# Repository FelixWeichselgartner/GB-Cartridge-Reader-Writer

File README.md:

# GB-Cartridge-Reader-Writer

This is an Arduino Shield, that can be used to dump GameBoy cartridges. This project is strongly inspired by this project:

* https://www.insidegadgets.com/2011/03/19/gbcartread-arduino-based-gameboy-cart-reader-%E2%80%93-part-1-read-the-rom/
* https://github.com/insidegadgets/GBCartRead

The code in this repo is based on this, however I did a lot of changes to the Arduino code.

# Tested ROMs

| Game                   | Dump ROM | Dump RAM | Upload RAM |
|------------------------|----------|----------|------------|
| Tetris (no MBC)        | yes      | N/A      | N/A        |
| Yoshi's Cookie (MBC1)  | yes      | N/A      | N/A        |
| Pokémon Red (MBC5)     | yes      | ?        | ?          |
| Pokémon Yellow (MBC5)  | yes      | yes      | ?          |
| Pokémon TCG (MBC5)     | yes      | yes      | ?          |

GBC is not supported so far.

# Eagle Layout for the Arduino shield

The bottom layer is supposed to be wired with a simple wire to be able to use a single layer pcb.

Used libraries (see submodules):

* https://github.com/adafruit/Adafruit-Eagle-Library
* https://github.com/robelix/rlx-eagle-libs
* https://github.com/JRodrigoTech/Eagle-Libraries

# License

Copyright (c) 2011-2016 by insideGadgets

Copyright (c) 2019-2020 by Felix Weichselgartner (on the changes)

Creative Commons - Attribution-NonCommercial 3.0 Unported (see License.txt)

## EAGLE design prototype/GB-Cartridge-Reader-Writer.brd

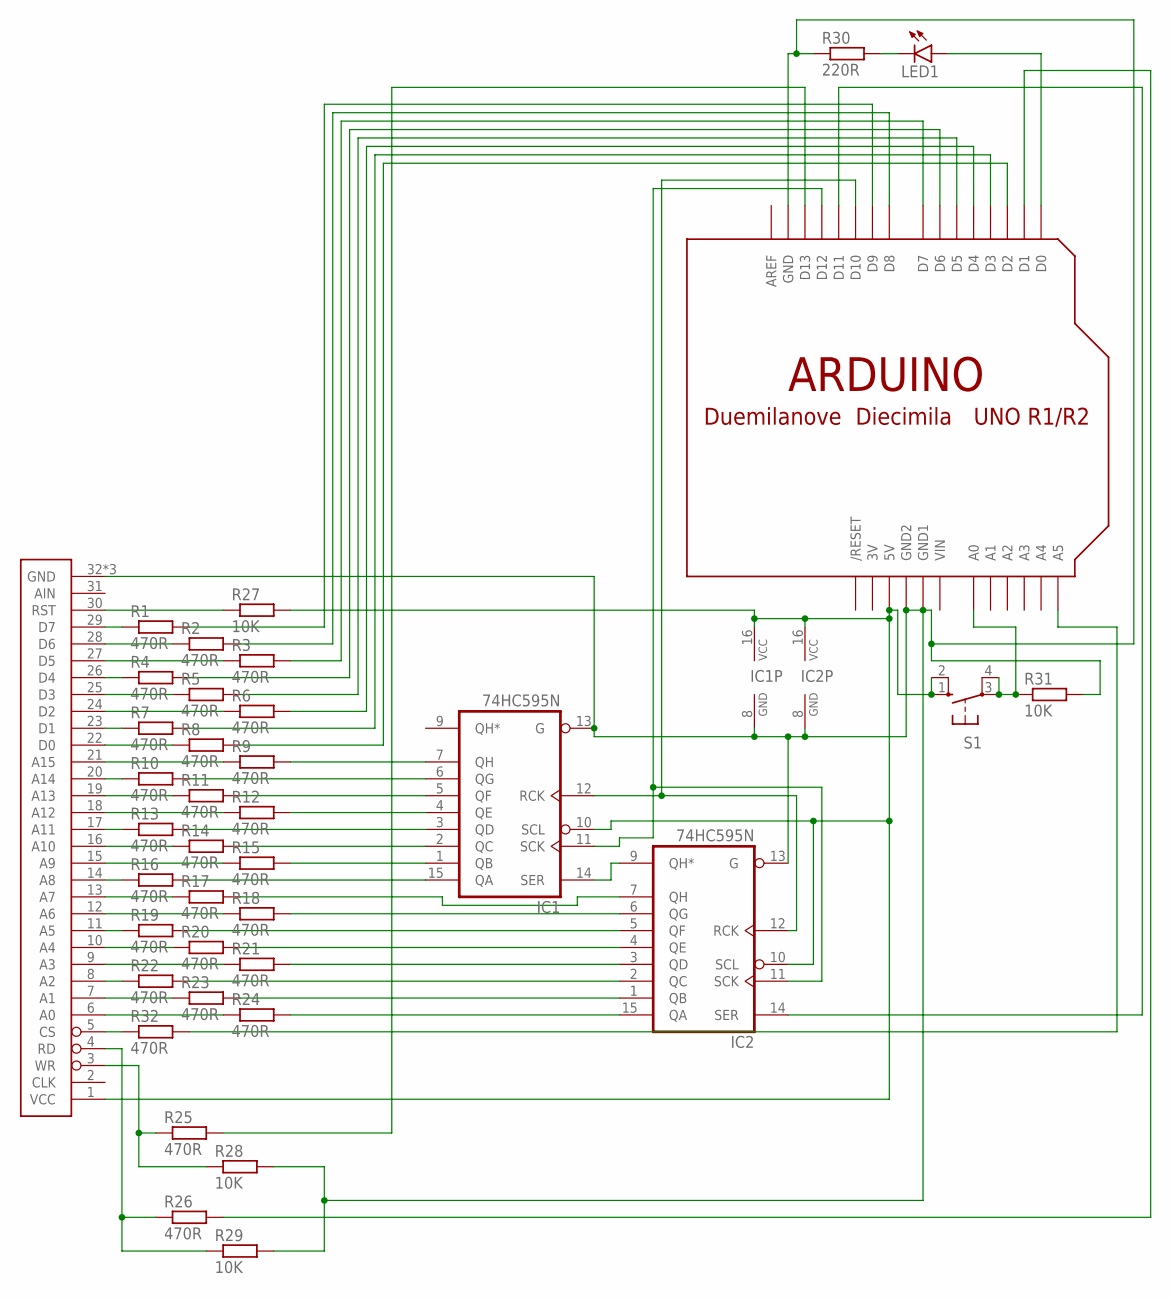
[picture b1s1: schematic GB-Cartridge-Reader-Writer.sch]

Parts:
IC1, IC2: 74HC595N; DIL16
LED1: LED5MM
R1, R2, R3, R4, R5, R6, R7, R8, R9, R10, R11, R12, R13, R14, R15, R16, R17, R18, R19, R20, R21, R22, R23, R24, R25, R26, R32: 470R; 0207/10
R27, R28, R29, R31: 10K; 0207/10
R30: 220R; 0207/10
S1: 10-XX; B3F-10XX
U$1: ARDUINO-NOHOLE
U$2: GB-CARTRIDGE-SLOTV3; GB-CARTRIDGE-SLOT-3

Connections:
3V: U$1.3V
unnamed: R1.1, U$2.29 (D7)
unnamed: R2.1, U$2.28 (D6)
unnamed: R3.1, U$2.27 (D5)
unnamed: R4.1, U$2.26 (D4)
unnamed: R5.1, U$2.25 (D3)
unnamed: R6.1, U$2.24 (D2)
unnamed: R7.1, U$2.23 (D1)
unnamed: R8.1, U$2.22 (D0)
unnamed: R9.1, U$2.21 (A15)
unnamed: R10.1, U$2.20 (A14)
unnamed: R11.1, U$2.19 (A13)
unnamed: R12.1, U$2.18 (A12)
unnamed: R13.1, U$2.17 (A11)
unnamed: R14.1, U$2.16 (A10)
unnamed: R15.1, U$2.15 (A9)
unnamed: R16.1, U$2.14 (A8)
unnamed: R17.1, U$2.13 (A7)
unnamed: R18.1, U$2.12 (A6)
unnamed: R19.1, U$2.11 (A5)
unnamed: R20.1, U$2.10 (A4)
unnamed: R21.1, U$2.9 (A3)
unnamed: R22.1, U$2.8 (A2)
unnamed: R23.1, U$2.7 (A1)
unnamed: R24.1, U$2.6 (A0)
unnamed: IC2.15 (QA), R24.2
unnamed: IC2.1 (QB), R23.2
unnamed: R32.1, U$2.5 (CS)
unnamed: IC2.3 (QD), R21.2
unnamed: IC2.4 (QE), R20.2
unnamed: IC2.2 (QC), R22.2
unnamed: IC2.6 (QG), R18.2
unnamed: IC2.7 (QH), R17.2
unnamed: IC2.5 (QF), R19.2
unnamed: IC1.1 (QB), R15.2
unnamed: IC1.2 (QC), R14.2
unnamed: IC1.15 (QA), R16.2
unnamed: IC1.4 (QE), R12.2
unnamed: IC1.5 (QF), R11.2
unnamed: IC1.3 (QD), R13.2
unnamed: IC1.7 (QH), R9.2
unnamed: R1.2, U$1.D9
unnamed: IC1.11 (SCK), IC2.11 (SCK), U$1.D12
unnamed: R27.1, U$2.30 (RST)
unnamed: R25.1, R28.1, U$2.3 (WR)
unnamed: R5.2, U$1.D5
unnamed: R26.2, U$1.D1
unnamed: R7.2, U$1.D3
unnamed: R8.2, U$1.D2
unnamed: IC1.14 (SER), IC2.9 (QH*)
unnamed: LED1.A, U$1.D0
unnamed: IC1.10 (SCL), IC1.16 (VCC), IC2.10 (SCL), IC2.16 (VCC), R27.2, S1.1 (S), S1.2 (S1), U$1.5V, U$2.1 (VCC)
unnamed: R6.2, U$1.D4
unnamed: R25.2, U$1.D13
unnamed: R4.2, U$1.D6
unnamed: R3.2, U$1.D7
unnamed: R2.2, U$1.D8
unnamed: LED1.K (C), R30.2
unnamed: IC1.12 (RCK), IC2.12 (RCK), U$1.D10
unnamed: IC1.6 (QG), R10.2
unnamed: IC2.14 (SER), U$1.D11
unnamed: IC1.8 (GND), IC1.13 (G), IC2.8 (GND), IC2.13 (G), R28.2, R29.2, R30.1, R31.2, U$1.GND, U$1.GND1, U$1.GND2, U$2.32 (GND), U$2.PAD1 (GND), U$2.PAD2 (GND)
unnamed: R26.1, R29.1, U$2.4 (RD)
unnamed: R32.2, U$1.A5
unnamed: R31.1, S1.3, S1.4 (P1), U$1.A0
VIN: U$1.VIN

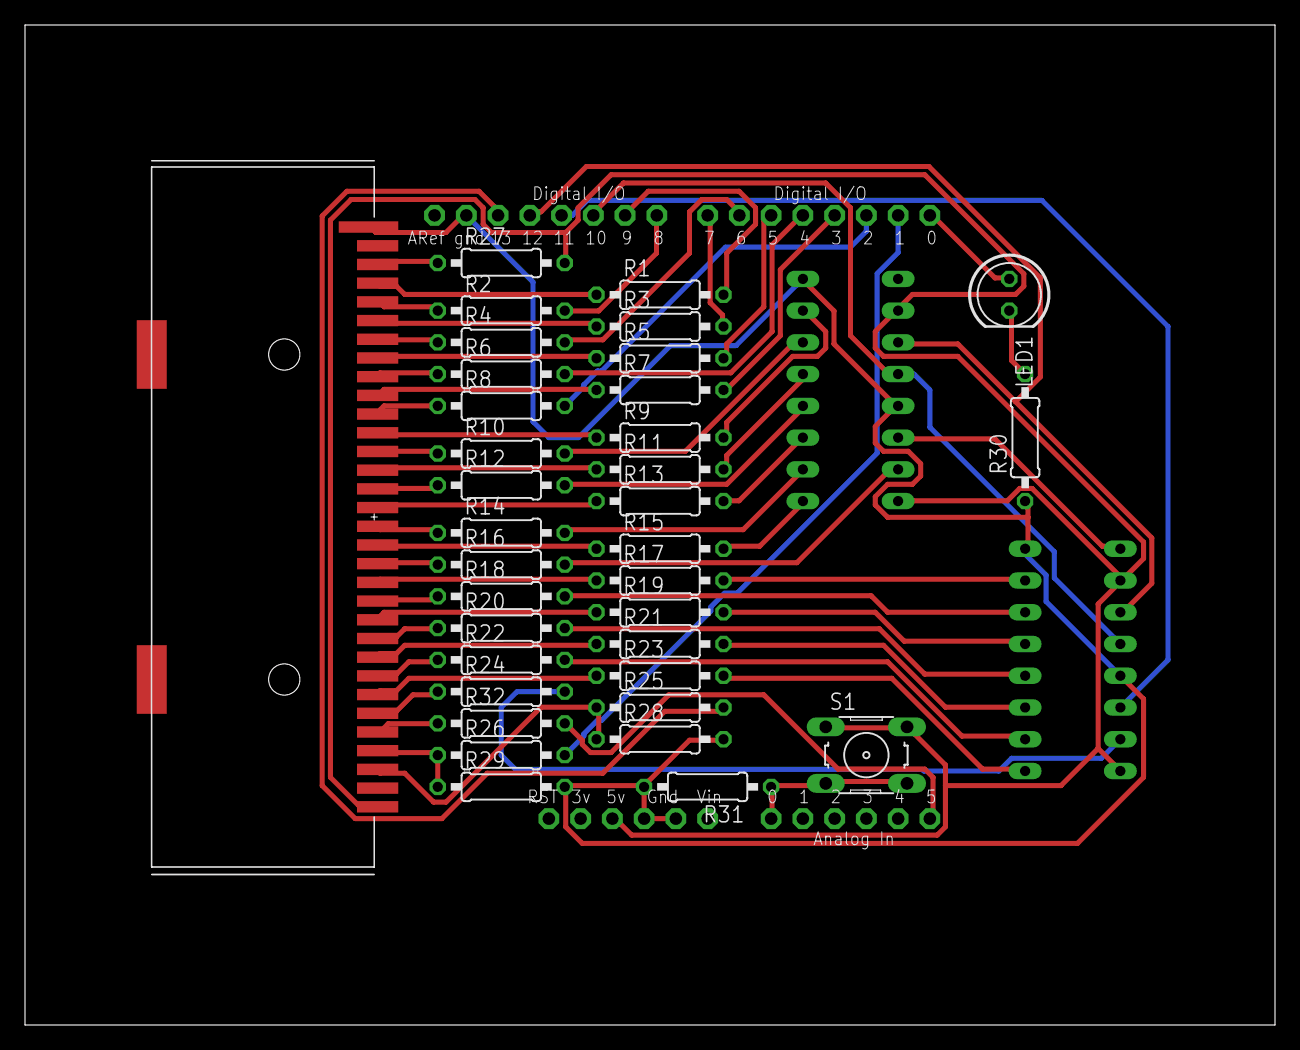
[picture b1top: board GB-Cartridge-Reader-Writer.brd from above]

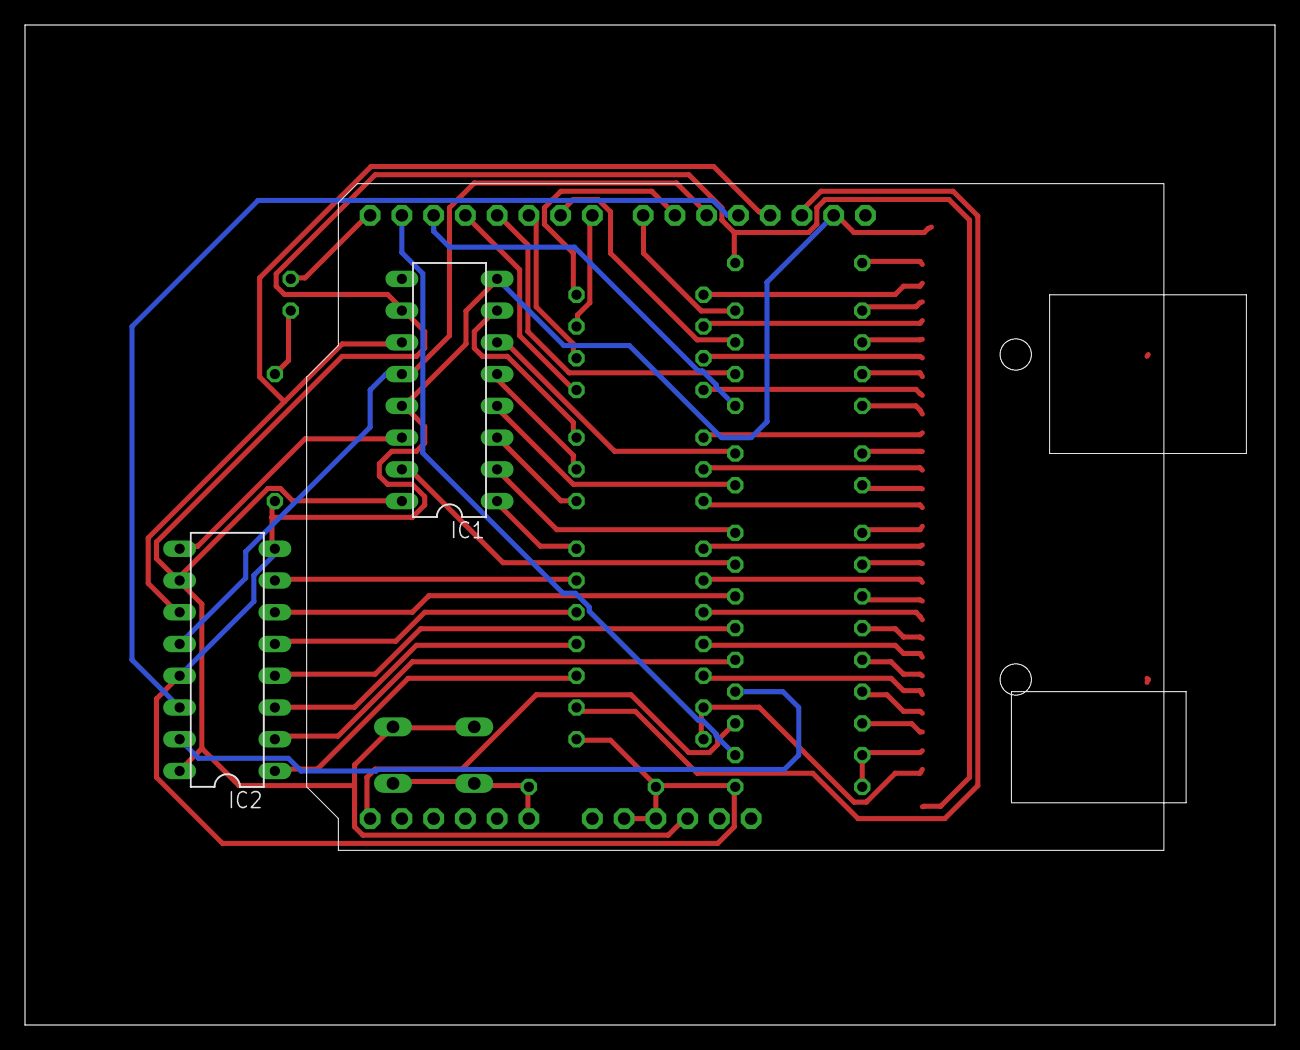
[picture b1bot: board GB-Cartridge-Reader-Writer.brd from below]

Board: 2 copper layers, 100.0 x 80.0 mm, 38 parts (2 on the bottom side), 64 nets.

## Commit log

2019-05-16 prototype with: smd->cart-adapter, tht->R,LED,BUTTON,SHIFT-REGISTERS
2019-05-18 moved some components - no functionial changes
2019-06-01 made traces wider; wired wire bridges on bottom layer to get the vias for drilling; more space between traces;
2019-06-17 moved one ic due to space issues
2019-08-03 firmware and python-interface - not working so far; shift-regs working, buttons & led working, error unknown
2019-08-04 still debug; may change shiftoutAddress and debug readByte;
2019-08-22 rom dumping now possible
2019-08-22 rom dumping fully working; writeByte working; -> next testing with games that have savegames
2019-09-09 class for better Cartridge handling
2019-09-10 compileable not tested yet
2019-09-12 formatting
2019-10-02 added missing destructor; linux option for com ports
2019-10-03 prepairing for update
2019-10-03 some changes that did not help POKECARD
2020-11-28 license, layout improvements, png, submodules, readme
2020-11-28 fixed typo
2020-11-28 added schematic from typo
2020-11-28 readme
2020-11-29 separated GPIO and cartridge class; table of tests
2020-11-29 fixed c&p error
2020-11-29 gbc not supported
2020-11-29 added pin tester sketch

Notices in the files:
parts and their libraries:
jrodrigo-gameboy: Creative Commons - Attribution and Share Alike 4.0 International - https://creativecommons.org/licenses/by-sa/4.0
